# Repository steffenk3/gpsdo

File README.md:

# gpsdo
Create a 10MHz reference clock disciplined by gps.
Based on work of Lars Walenius "What is Lars Arduino basd GPSDO Controller with 1ns TIC?"

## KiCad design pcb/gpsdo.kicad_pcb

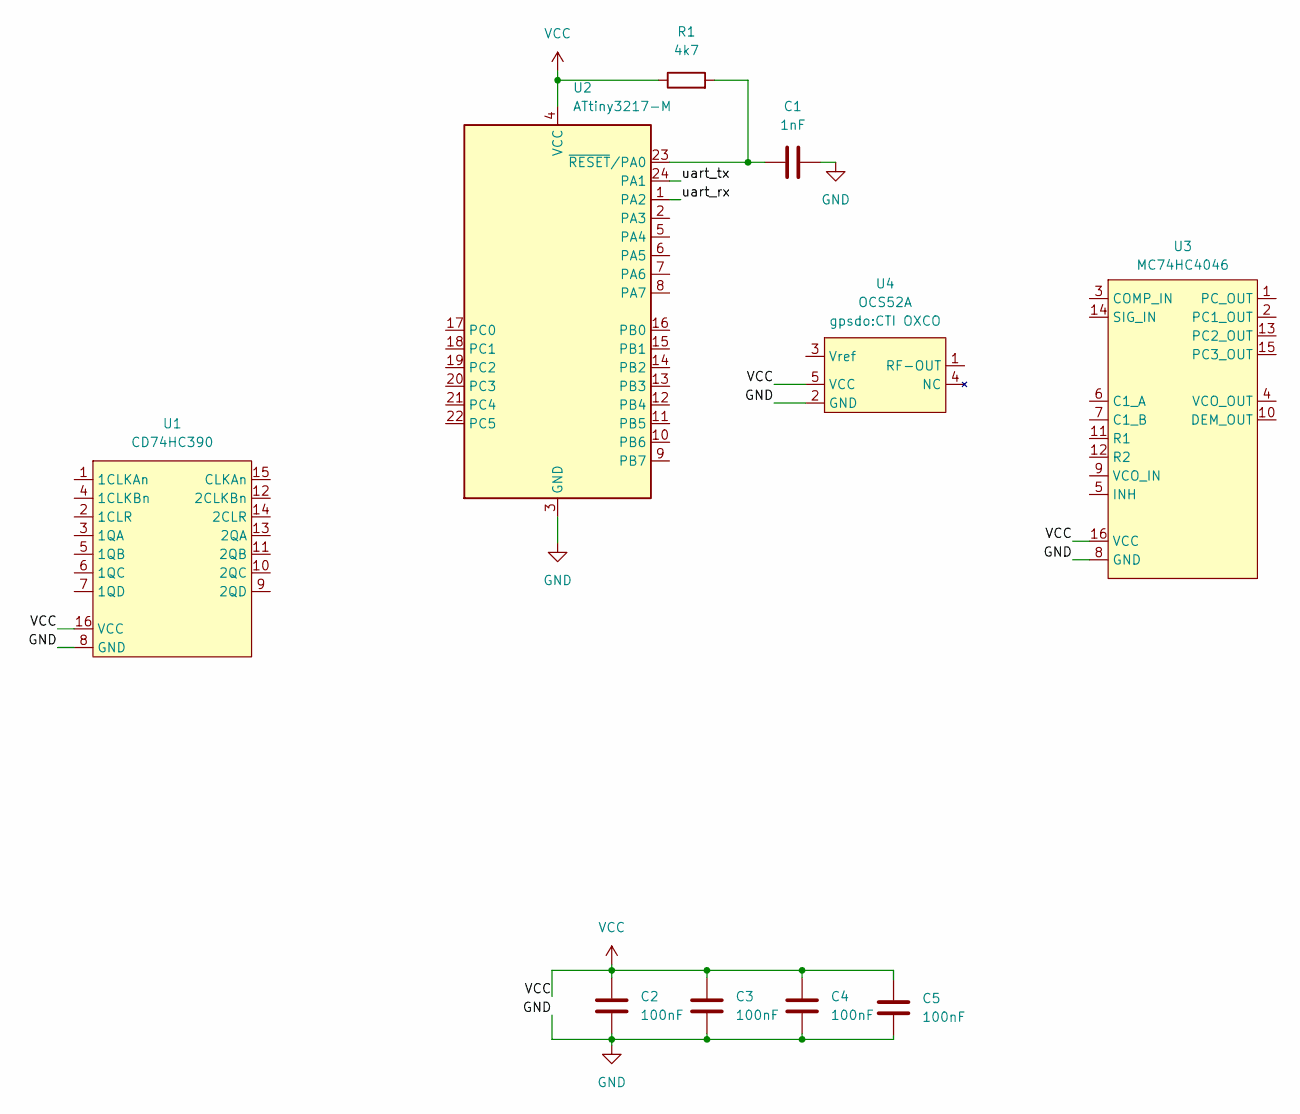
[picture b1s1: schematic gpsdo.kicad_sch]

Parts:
C1: 1nF; C_0805_2012Metric_Pad1.18x1.45mm_HandSolder
C2, C3, C4, C5: 100nF; R_0805_2012Metric_Pad1.20x1.40mm_HandSolder
R1: 4k7; C_0805_2012Metric_Pad1.18x1.45mm_HandSolder
U1: CD74HC390; DIP-16_300_ELL
U2: ATtiny3217-M; QFN-24-1EP_4x4mm_P0.5mm_EP2.6x2.6mm
U3: MC74HC4046; DIP-16_300_ELL
U4: OCS52A; CTI OXCO

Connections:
/uart_rx: U2.1 (PA2)
/uart_tx: U2.24 (PA1)
GND: C1.2, C2.2, C3.2, C4.2, C5.2, U1.8 (GND), U2.3 (GND), U2.25 (GND), U3.8 (GND), U4.2 (GND)
unnamed: C1.1, R1.2, U2.23 (~RESET/PA0)
VCC: C2.1, C3.1, C4.1, C5.1, R1.1, U1.16 (VCC), U2.4 (VCC), U3.16 (VCC), U4.5 (VCC)

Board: 2 copper layers, 10 parts (0 on the bottom side), 3 nets, no tracks yet.

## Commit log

2022-11-24 add first design files
2022-11-24 started layout
